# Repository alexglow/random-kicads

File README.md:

# random-kicads
KiCad projects that don't go anywhere else.

## avnet-pick
Guitar pick PCB for Avnet's centennial celebration, in honor of the time they owned Guild Guitars. Works as an earring / key fob / etc., and lights up green! See the full project on Hackster at bit.ly/avnetpick

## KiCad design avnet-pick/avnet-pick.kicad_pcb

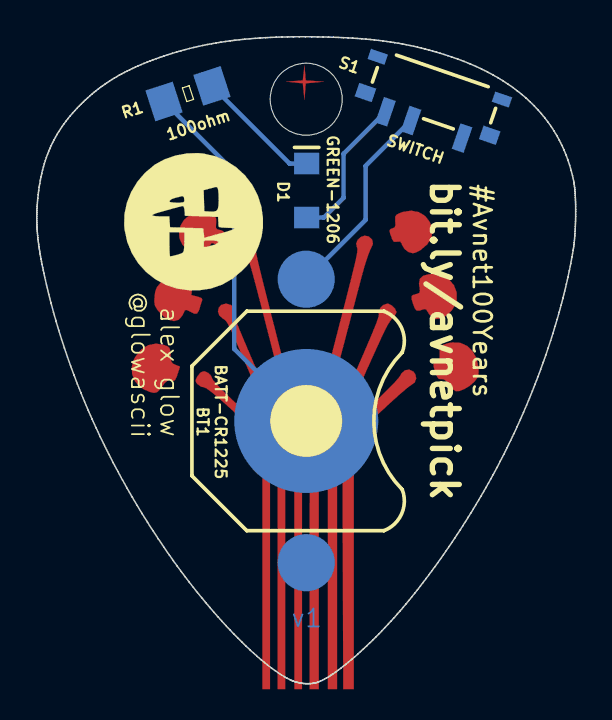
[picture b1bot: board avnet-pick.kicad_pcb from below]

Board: 2 copper layers, 29.9 x 35.9 mm, 5 parts (5 on the bottom side), 4 nets.

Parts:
 : hlogoTiny
BT1: BATT-CR1225; BATTCON_12MM
D1: GREEN-1206; LED-1206
R1: 100ohm; 1206
S1: SWITCH; SWITCH_SPST_SMD_A

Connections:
unnamed: BT1.GND, R1.2
unnamed: BT1.PWR@, S1.2
unnamed: D1.A, S1.1
unnamed: D1.C, R1.1

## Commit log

2021-11-17 Add avnet pick project
